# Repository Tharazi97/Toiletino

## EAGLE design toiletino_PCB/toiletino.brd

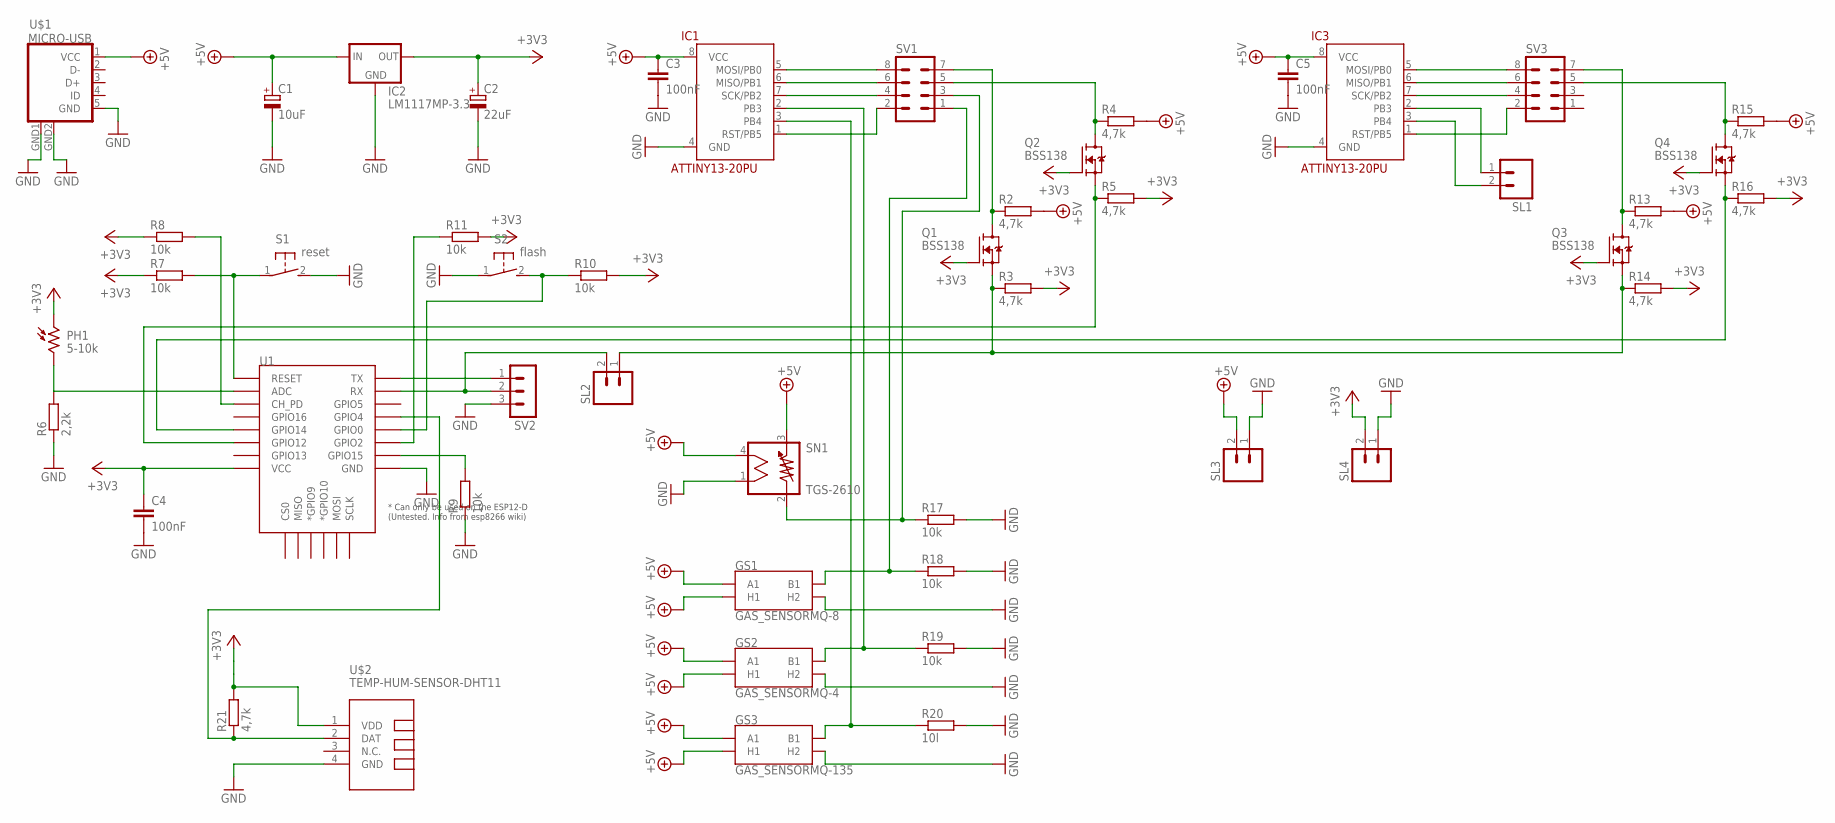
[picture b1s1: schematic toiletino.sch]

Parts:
C1: 10uF; E2,5-6
C2: 22uF; E2,5-6
C3, C4, C5: 100nF; C025-025X050
GS1: GAS_SENSORMQ-8; GAS_SENSOR
GS2: GAS_SENSORMQ-4; GAS_SENSOR
GS3: GAS_SENSORMQ-135; GAS_SENSOR
IC1, IC3: ATTINY13-20PU; DIL08
IC2: LM1117MP-3.3; SOT223
PH1: 5-10k; TO-5_V10
Q1, Q2, Q3, Q4: BSS138; SOT23
R2, R3, R4, R5, R13, R14, R15, R16, R21: 4,7k; 0207/10
R6: 2,2k; 0207/10
R7, R8, R9, R10, R11, R17, R18, R19: 10k; 0207/10
R20: 10l; 0207/10
S1: reset; DTS-3
S2: flash; DTS-3
SL1, SL2, SL3, SL4: MA02; 02PA
SN1: TGS-2610
SV1, SV3: MA04-2
SV2: MA03-1
U1: ESP12ESMD; ESP12E-SMD
U$1: MICRO-USB
U$2: TEMP-HUM-SENSOR-DHT11

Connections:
+3V3: C2.+, C4.1, IC2.2 (OUT), IC2.4 (OUT), PH1.1, Q1.1 (G), Q2.1 (G), Q3.1 (G), Q4.1 (G), R3.2, R5.2, R7.1, R8.1, R10.2, R11.2, R14.2, R16.2, R21.2, SL4.2, U1.VCC, U$2.1 (VDD)
+5V: C1.+, C3.1, C5.1, GS1.A1, GS1.A2 (A1), GS1.HA (H1), GS2.A1, GS2.A2 (A1), GS2.HA (H1), GS3.A1, GS3.A2 (A1), GS3.HA (H1), IC1.8 (VCC), IC2.3 (IN), IC3.8 (VCC), R2.2, R4.2, R13.2, R15.2, SL3.2, SN1.3, SN1.4, U$1.1 (VCC)
GND: C1.-, C2.-, C3.2, C4.2, C5.2, GS1.HB (H2), GS2.HB (H2), GS3.HB (H2), IC1.4 (GND), IC2.1 (GND), IC3.4 (GND), R6.1, R9.1, R17.2, R18.2, R19.2, R20.2, S1.2, S2.1, SL3.1, SL4.1, SN1.1, SV2.3, U1.GND, U$1.5 (GND), U$1.GND1 (GND), U$1.GND2 (GND), U$2.4 (GND)
unnamed: IC1.1 (RST/PB5), SV1.2
unnamed: IC1.7 (SCK/PB2), SV1.4
unnamed: IC1.6 (MISO/PB1), SV1.6
unnamed: IC1.5 (MOSI/PB0), SV1.8
unnamed: Q2.3 (D), R4.1, SV1.5
unnamed: Q1.3 (D), R2.1, SV1.7
unnamed: Q1.2 (S), Q3.2 (S), R3.1, R14.1, SL2.1
unnamed: Q2.2 (S), R5.1, U1.GPIO12
unnamed: SV2.1, U1.TXD0 (TX)
unnamed: PH1.2, R6.2, U1.ADC
unnamed: R7.2, S1.1, U1.RESET
unnamed: R8.2, U1.CH_PD
unnamed: R9.2, U1.GPIO15
unnamed: R11.1, U1.GPIO2
unnamed: R10.1, S2.2, U1.GPIO0
unnamed: IC3.1 (RST/PB5), SV3.2
unnamed: IC3.7 (SCK/PB2), SV3.4
unnamed: IC3.6 (MISO/PB1), SV3.6
unnamed: IC3.5 (MOSI/PB0), SV3.8
unnamed: Q4.3 (D), R15.1, SV3.5
unnamed: Q3.3 (D), R13.1, SV3.7
unnamed: Q4.2 (S), R16.1, U1.GPIO14
unnamed: R17.1, SN1.2, SV1.3
unnamed: IC3.2 (PB3), SL1.1
unnamed: IC3.3 (PB4), SL1.2
unnamed: GS1.B1, GS1.B2 (B1), R18.1, SV1.1
unnamed: R21.1, U1.GPIO4, U$2.2 (DAT)
unnamed: GS2.B1, GS2.B2 (B1), IC1.2 (PB3), R19.1
unnamed: SL2.2, SV2.2, U1.RXD0 (RX)
unnamed: GS3.B1, GS3.B2 (B1), IC1.3 (PB4), R20.1

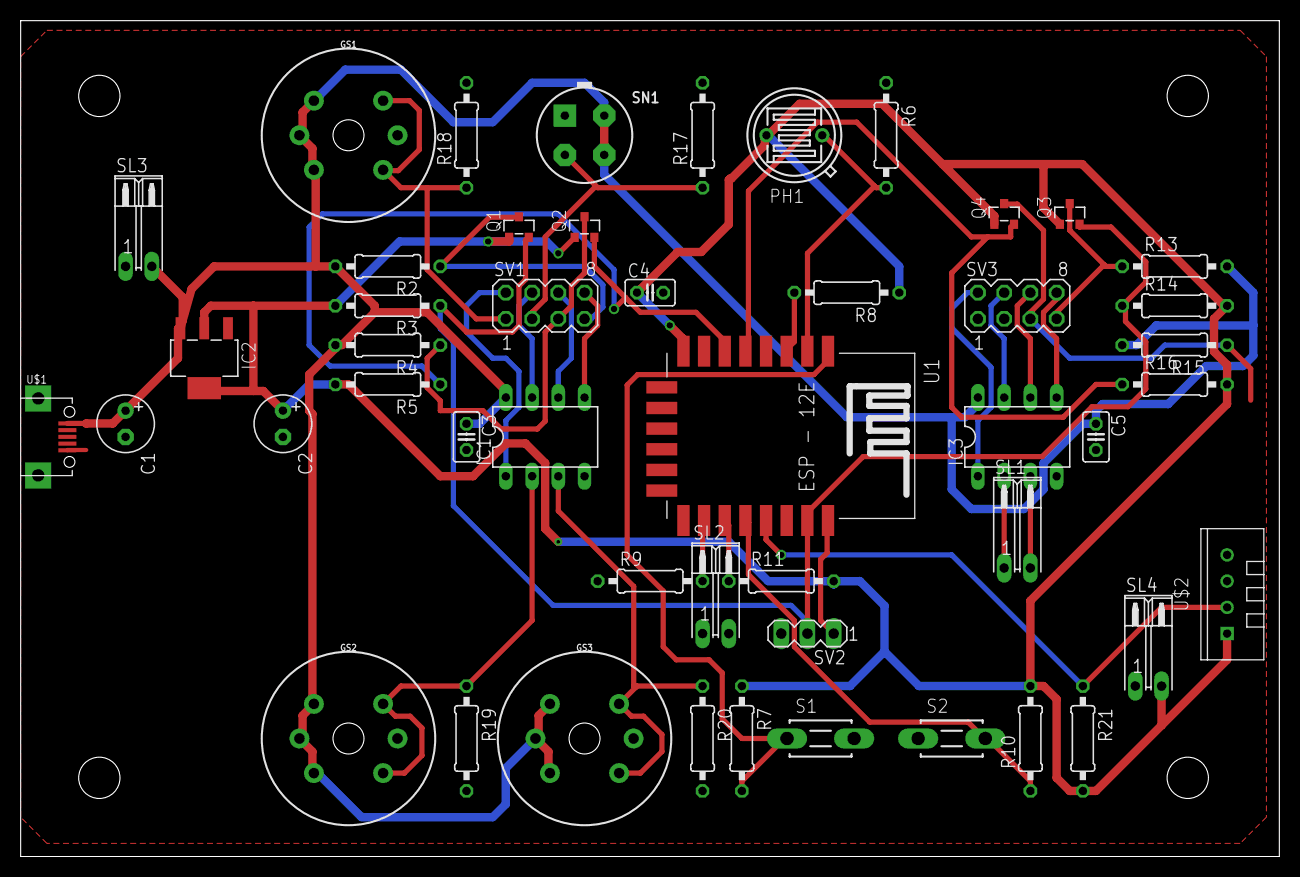
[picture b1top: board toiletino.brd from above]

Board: 2 copper layers, 121.9 x 81.0 mm, 48 parts (0 on the bottom side), 33 nets.

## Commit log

2020-04-03 Add ATtiny code
    Read 4 sensors and send them through bit banging UART.
    ADC0 needs to be turned on later.
2020-04-03 Add ESP12 code
    ESP communicates with ATtiny and DHT sensor. Collects their readings
    and sends it to the database.
2020-04-03 Add webpage files
    The webpage uses SQL to receive data series from the server and display
    it as graphs.
2020-06-24 Add EAGLE project
2020-06-24 Decrease baud rate
    Decrease baud rate to improve error ratio.
2020-06-24 Update ESP to local and global version
    Changed baud rate to communicate with ATiny too
2020-06-24 Tweak in showing graphs
2020-06-24 Add normalization of data
2020-06-24 Change mobile version of a page

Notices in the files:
parts and their libraries:
SparkFun-Sensors: Licensing: Creative Commons ShareAlike 4.0 International - https://creativecommons.org/licenses/by-sa/4.0
diy-modules: Released under the Creative Commons Attribution 4.0 International License: http://creativecommons.org/licenses/by/4.0
